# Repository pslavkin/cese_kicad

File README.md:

# cese_kicad
tp para cese sobre kicad

Autor: Pablo Slavkin
CESE2018

Driver motores paso a paso
===========================

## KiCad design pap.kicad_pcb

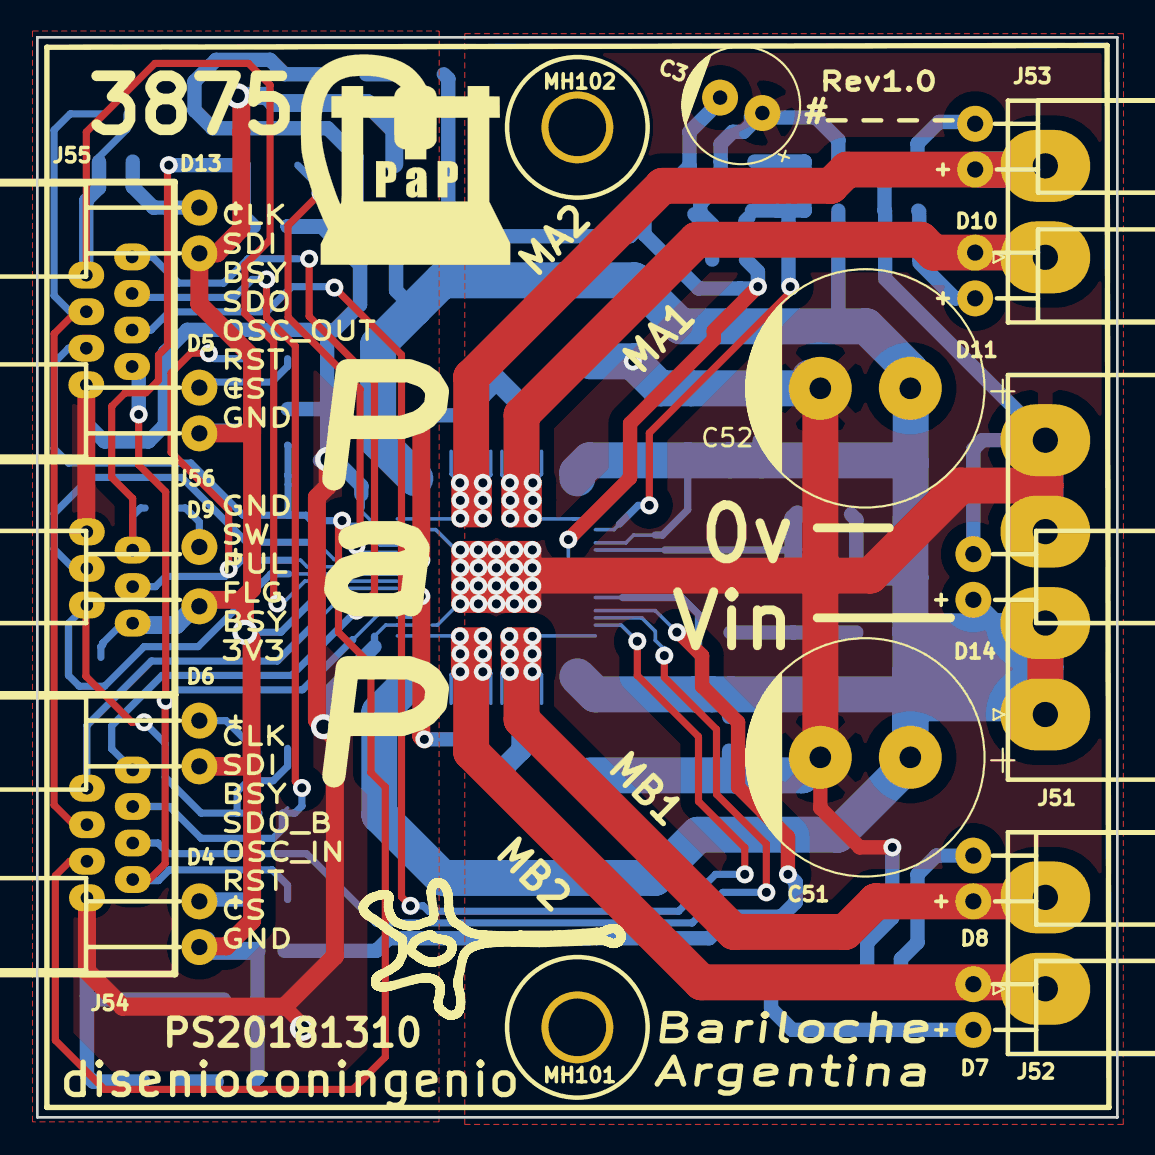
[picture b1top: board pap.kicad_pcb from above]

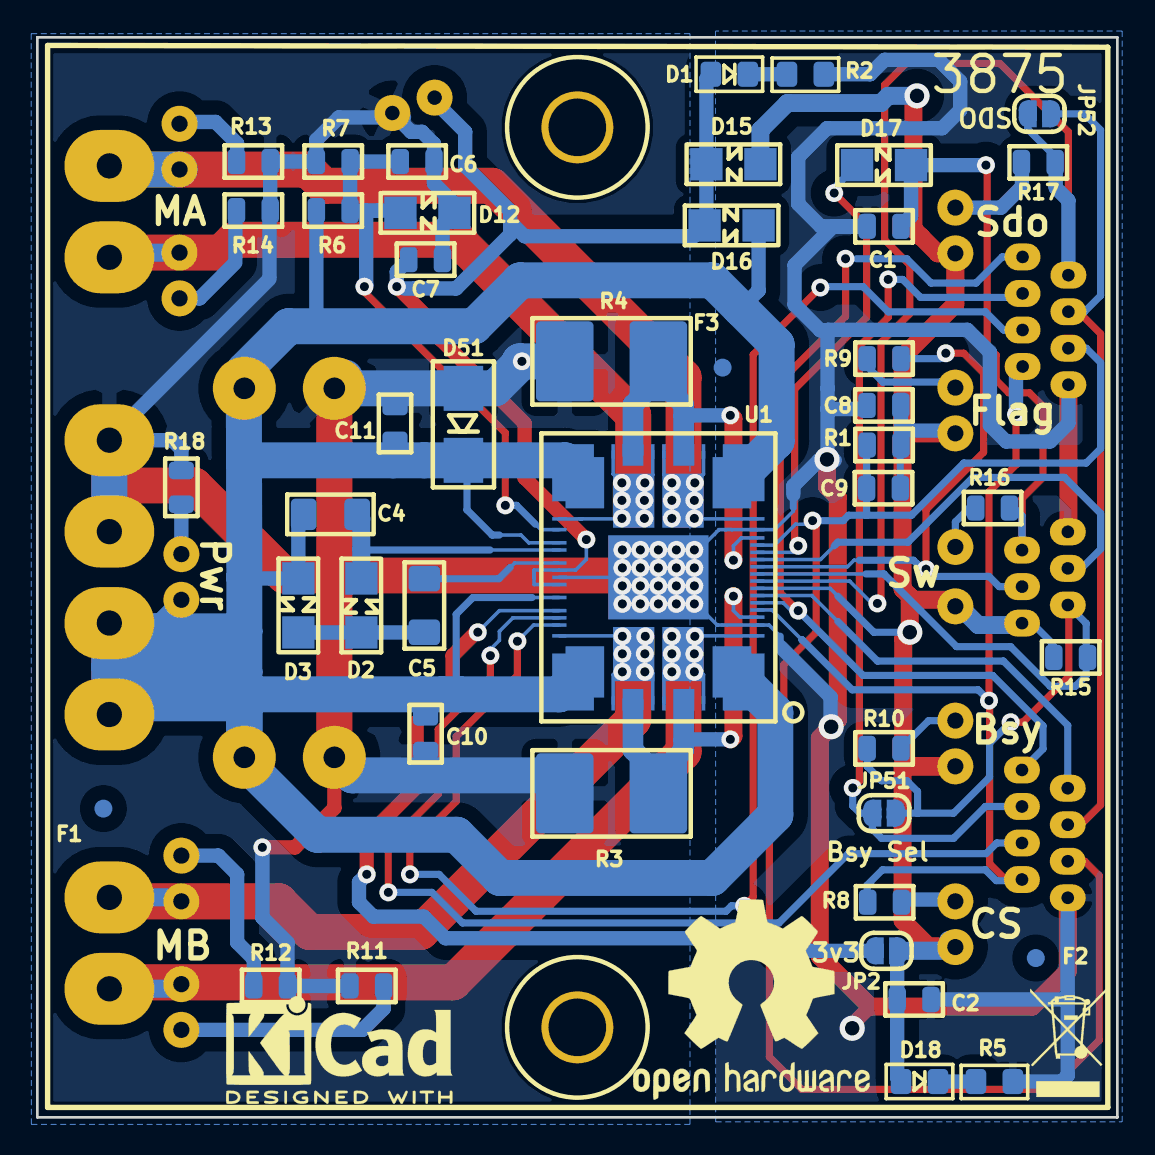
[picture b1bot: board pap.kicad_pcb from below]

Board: 2 copper layers, 60.0 x 60.0 mm, 72 parts (49 on the bottom side), 42 nets.

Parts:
C1: 10n; C_0805_2012Metric
C2, C6, C7, C8, C9, C10, C11: 100n; C_0805_2012Metric
C3: 220uFx25v; CP_Radial_D6.3mm_P2.50mm
C4, C5: 220n; C_1206_3216Metric_Pad1.42x1.75mm_HandSolder
C51, C52: 100uFx100v; CP_Radial_D13.0mm_P5.00mm
D1, D18: LED_SMD; Wo_Paste_LED_0805_2012Metric_Pad1.15x1.40mm_HandSolder
D2, D3, D15, D16, D17: LL4148; D_MiniMELF
D4, D13: LED; led5x2_rj_verde
D5, D6: LED; led5x2_rj_amarillo
D7: LED; led5x2_enchufable_amarillo
D8: LED_I; led5x2_enchufable_verde
D9: LED; led5x2_rj_rojo_abierto
D10: LED_I; led5x2_enchufable_amarillo
D11: LED; led5x2_enchufable_verde
D12: 3v3; D_MiniMELF
D14: LED_I; led5x2_enchufable_rojo
D51: SM4007; D_SMA
F1, F2, F3: Fiducial; Fiducial_1mm_Dia_2mm_Outer
J51: Conn_01x04; PhoenixContact_MSTBA_2,5_4-G-5,08_1x04_P5.08mm_Horizontal
J52, J53: Conn_01x02; PhoenixContact_MSTBA_2,5_2-G-5,08_1x02_P5.08mm_Horizontal
J54, J55: RJ45; rj45
J56: RJ12; rj12
JP2, JP51, JP52: jumper; SolderJumper-2_P1.3mm_Open_RoundedPad1.0x1.5mm
L101: logo_dci; logo_neurona_15mm
L102: logo_kicad; KiCad-Logo2_6mm_SilkScreen
L104: logo_cnc; cnc
L401: logo_recyclado; WEEE-Logo_4.2x6mm_SilkScreen
LOGO103: Logo_Open_Hardware_Small; OSHW-Logo2_14.6x12mm_SilkScreen
MH101, MH102: 3mm; MountingHole_3.2mm_M3
NT51, NT52: Net-Tie_2; NetTie-2_SMD_Pad0.2mm_sin_seri
R1, R11, R12, R13, R14, R18: 10k; R_0805_2012Metric
R2: 1k5; Wo_Paste_R_0805_2012Metric_Pad1.15x1.40mm_HandSolder
R3, R4: 0.1e; R_2816_7142Metric_Pad3.20x4.45mm_HandSolder
R5: 100e; Wo_Paste_R_0805_2012Metric_Pad1.15x1.40mm_HandSolder
R6: 100k; R_0805_2012Metric
R7: 3k3; R_0805_2012Metric
R8, R9, R10, R16, R17: 100e; R_0805_2012Metric
R15: R; R_0805_2012Metric
U1: powerstep01; powerstep

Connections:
3V3: C2.2, C8.2, C9.2, D4.2, D5.2, D6.2, D9.2, D13.2, D15.2, D18.1, J56.1, JP2.1, R1.2, R15.2, U1.13
15v: C3.2, C7.2, D1.1, D15.1, D16.2, U1.58, U1.60
85v: C4.2, C10.2, C11.2, C51.1, C52.1, D3.2, D14.1, D16.1, D51.1, J51.1, J51.2, R6.1, U1.32, U1.43, U1.55, U1.61, U1.75, U1.86
/connector/Busy: J56.2, JP51.2, R10.1, R15.1, U1.15
/connector/Busy_Out: J54.6, J55.6, JP51.1
/connector/CLK: J54.8, J55.8, U1.11
/connector/CS: J54.2, J55.2, R8.1, U1.10
/connector/Flag: J56.3, R9.1, U1.16
/connector/MotorA1: D11.2, J53.1, U1.38, U1.42, U1.53, U1.92
/connector/MotorA2: D10.1, J53.2, U1.22, U1.33, U1.37, U1.91
/connector/MotorB1: D8.1, J52.2, U1.65, U1.76, U1.80, U1.94
/connector/MotorB2: D7.2, J52.1, U1.7, U1.81, U1.85, U1.90
/connector/Osc_In: J54.4, U1.63
/connector/Osc_Out: J55.4, U1.64
/connector/Pulse: J56.4, U1.17
/connector/Reset: C9.1, J54.3, J55.3, R1.1, U1.19
/connector/SDI: J54.7, U1.12
/connector/SDO: J55.7, JP52.1, R17.1, U1.14
/connector/Sdo_Back: J54.5, J55.5, JP52.2
/connector/Switch: C1.2, D17.1, J56.5, R16.1
/motor/Adc: C6.2, D12.1, R6.2, R7.1, U1.54
/motor/Cpump: C5.1, U1.57
/motor/SenseA: R4.1, U1.20, U1.35, U1.40
/motor/SenseB: R3.1, U1.9, U1.78, U1.83
/motor/Switch_Local: D17.2, U1.18
/motor/Vboot: C4.1, D2.1, U1.56
G3V3: C1.1, C2.1, C8.1, J54.1, J55.1, J56.6, NT51.2, NT52.2, R2.1, R5.1, U1.8, U1.21
G85V: C3.1, C6.1, C7.1, C10.1, C11.1, C51.2, C52.2, D12.2, D51.2, J51.3, J51.4, NT51.1, NT52.1, R3.2, R4.2, R7.2, R11.1, R12.1, R13.1, R14.1, R18.1, U1.59, U1.93
unnamed: C5.2, D2.2, D3.1
unnamed: D1.2, R2.2
unnamed: D4.1, R8.2
unnamed: D5.1, R9.2
unnamed: D6.1, R10.2
unnamed: D7.1, R11.2
unnamed: D8.2, R12.2
unnamed: D9.1, R16.2
unnamed: D10.2, R13.2
unnamed: D11.1, R14.2
unnamed: D13.1, R17.2
unnamed: D14.2, R18.2
unnamed: D18.2, R5.2
Vreg: JP2.2, U1.62

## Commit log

2018-09-22 creo symbolo powerstep y arranco a conectar al tiempo de diseniar
    agregue el symbolo del powerstep.. lo hice siguiendo la secuencia de
    pines originales porque me permite utilizar la simetria del chip y ya ir
    pensando en el ruteo, el modo de reorganizar los pines que hizo el
    fabricante quedo igual o peor de desordenado.. prefiero este que ya me
    ayuda a ir viendo la disposicion y ademas aprovechar la simetria. estoy
    viendo como hacer el encadenamiento de spi y clk.. no se si utilizar
2018-09-23 agrego mas conectores y paso a pcb (todo mal!)
    agregue conectores RJ45 para el encadenamiento spi y busyflag, pero no
    para pulse.. es lo voy a mandar aparte porque es individual por cada
    driver.. al igual que switch, y vere si alguna cosa mas.. en el rj me
    sobran aun 2 pines.. ya vere que mando..lastima que no puedo mandar
    pulse por ahi.. porque al ser 1 por driver necesito ir directo desde el
    controlador.. sino como?... pase a pcb para ver que onda nada mas y
2018-09-24 armo huella step01 y asigno casi todas las huellas
    ahi hice el landpattern del steo01, que es un parto, pero quedo bueno..
    al tiempo que aprendi a editar y la verdad es que es comodo.. me animo a
    decir que supera a allegro, y de hecho se parece demasiado en muchas
    cosas.. huele a copia de algun lado.. incluiso los nombres en los menus
    son iguales... como sea, ya quedo eso, lo que si tuve que volar algunos
    pines repetidos en el simbolo porque sino era un chino tener muchos
2018-09-25 arranco a rutear, cambio xtal por SMD y opcion CLKIN
    arranque a tirar pist porque me estaba aburriendo ya, de paso voy
    practivcando los shortcuts y demas.. esta muy copado y te aviso.. es
    plagio a allegro.. no cabe dudas.. como sea, cambie el Xtal por uno SMD
    de 4 pines que se consigue y minimiza el espacio, agegue tambien clkin
    para mandar clk a todos por igual con el PWM del uC para sincronizar con
    un selector para poder usar el xtal si es que el PWM se pierde por
2018-09-29 Cambio Rj's vuela xtal, entra Reset, agrego tornillos
    Hago de todo un poco entre lo que saco el xtal porque ya probe que no se
    necesita, elijo un IC que gnere 16Mhz y lo encadeno al resto, el RJ lo
    cambie por otra que se parece mas a la que voy a usar, pero hay que
    verificar, agregue un selector de osc, y agregue unos agujeros de
    tornillos que no se si los quiero. va bien.. tengo que meterle mas al
    ruteo
2018-10-05 cambio nombres, hago board edge, defino capas, posicion y demas
    hice de todo un poco, principalmente le di forma a la placa con una
    dimensino pasable, ajuste los conectores que aun no me convencen, pero
    cambie la entrada para el conector de 4 y los motores en 2 de 2, cosa
    que la alimentacion este toda en un solo conector y me queda piola para
    que los motores salgan del IC para los costados. en cuanto a la logica
    aun no me decido si voy a poner otra RJ para la salida d busy y demas o
2018-10-05 achico placa, agrego rj12, defino pistas, ruteo potencia
    ahi le voy dando forma. ya rute la potencia y esta mas o menios bien,
    ahora estoy viendo el tema de los leds para ponmerlos encima de los
    conectores con patas porque es la mejor opcion que se me ocurrio y ya la
    tengo probada.. con leds SMD despues tengo que hacer un chino para
    sacarlo para afuera y de costado necesito acrilico puro para conducir..
    es mas laburo.. con patas hago 2x1.. veremos como queda
2018-10-05 sigo ruteando y acomodando ocsas, agrego algunos leds
2018-10-06 ruteo!! no se como pero esta todo conectado!, horrible claro
    conecto todo.. bastamte ofiero pero conecto.. y quedan huevos para ir
    mejorando.. tampoco esta taaaan mal... y las cosas ya estan en su
    lugar.. me quedan varias horas para pulir todo y respetar las reglas de
    cada net y demas.. queda un pedazo todavia pero no esta nada mal..
    lo que si me di cuenta que estaba pensando mal lo de la cadena de spi y
    la de osci, ahora es simple, ficha de in y ficha de out, por la de in
2018-10-13 sigo ruteando, serigrafia mas gruesa, alineacino etc
2018-10-13 agregando mascaras para alambrado de pistas tie-net,
    agregando mascaras para soldar alambres en pistas de potencia, uno con
    tie net gnd de 3 con el gnd de 85, tambien agrego planos de tierra para
    ambos, y asuntos relacionados con eso. mejor el 3d de las rj;s, agrego
    gerbers del fabricante, recien lo veo!! pero se parece bastante a lo que
    hice..
2018-10-13 cambio de nombres, mejorop serigrafia, agrego pin
    agrego el pin de flag ya que me sobraba un pin en el RJ12, cambio los
    nombres de 0-50 para motor y 51 a 100 para conector, ajusto el espesor
    de la seri, y algunas cosas mas..
2018-10-14 aghrego serigrafia, logos, faltan fiduciales aun
2018-10-14 voy terminando, me falta sacar los gerbers.. a por ellos...
2018-10-14 agrego gerbers.. va quedando peeero falta crc de layout
    ahi lo voy liquidando, me convence, pero me falta tirar el crc en layout
    que tiene muchos errores principalmente por el tema de que para una
    misma net tengo varias restriccinoes solapadas.. vere como hago con eso
    y lo cierro.. ser maniana.. me estoy durmiendo..
    ha, cambio tambien un poco la jerarquia de dirs asi queda mas ordenadito
2018-10-14 me habia olvidado algunos capas, agrego leds, me falta aun
    no estaba poniendo los descaoples de los reguladores internos y hay uno
    de 220uF! ese lo mando TH, igual voy a verificar en el PCB de st. pero
    igual me faltaban tambien los capas de 3v3 y 85v tambien.. veo donde los
    meto
2018-10-18 termino ruteo, genero gerbers y drills, y entrego
    Listo pisto, lo dejo asi, ya lo revise varias veces, agregue los
    desacoples y el bulk pendiente, coloreo leds con nuevo 3d, genero
    gerners, y agrego valores a los componentes. ha y tambien dejo PTH los
    agujeros de los tornillos, quedan mejor. y no mucho mas.. entrego ya!
2018-10-19 agreo fabricante y algun detalle menor en pcb
    solo agrego unos detalles en fab de pcb indicando vias, pistas y
    tecnologia de fabricacion. algo tenia, completo algun detalle mas
2018-10-19 reviso y ajusto minimo track global a 0.25
    en realidad el iC requiere de track de 0.2, pero el resto de la placa
    intento llegar a 0.25 para tecnologia de 10/10 mils, y generalmente se
    acepta que para el integrado sea un poco mayor que para el ruteo.
    veremos.. lo dejo en 0.25/0.25
2018-10-19 agrego imaen en readme
2018-10-19 error en el path de pics en Readme, corrijo
2018-10-22 agfego valores faltantes de capas
    Gracias al aporte de Gonzalo, me habian quedado algunos capas sin valor.
    .Corrijo. Hay otras sugerencias de Gonzalo que no se corrigen, solo se
    consideran y se evaluaran luego
2018-11-28 Agrego modelos 3d locales, y corrijo lo solicitado por Diego
    Ahi agregue las correcciones que me paso Diego y agregue los modelos 3d
    en el repo local que no estaban. el resto fueron ajustes menores.
    Tambien agregue las fotos del proto fabricado
